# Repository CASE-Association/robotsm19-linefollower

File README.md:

# CASE line follower robot 2019
Project repository for CASE hardware and software developement for attending the Swedish Robotic Championship 2019.
The robot got 2nd place in the Swedish Robotic Championship 2019.

### Contributors
    -   Oskar Johansson
    -   Isak Åslund 
    -   Stefan Larsson

### Structure
    -   Software - All code for running the robot, implemented on Arduino   
    -   Hardware - PCB and hardware design
        -   Schematics for Arduino & STM32F103C8

### Pictures
[Picture album](https://imgur.com/a/kjrejrC)

**V0.1**

**V0.2**

**V1.0**

**PCB**
Two PCBs was designed, one for arduino and one for STM32.
Due to battery being applied to the VB pin on the STM32 it burned up. 
This caused us to use an arduino nano with breadboard instead. 
Since then a updated PCB has been made.

### Pinout Help
https://components101.com/microcontrollers/arduino-nano

### Info for development
IDE - Visual Studio Code + PlattformIO
If you want to simplify development change the formatter for cpp to the following:
"{ BasedOnStyle: Google, IndentWidth: 4, ColumnLimit: 0}", more info [here](https://stackoverflow.com/questions/46111834/format-curly-braces-on-same-line-in-c-vscode)

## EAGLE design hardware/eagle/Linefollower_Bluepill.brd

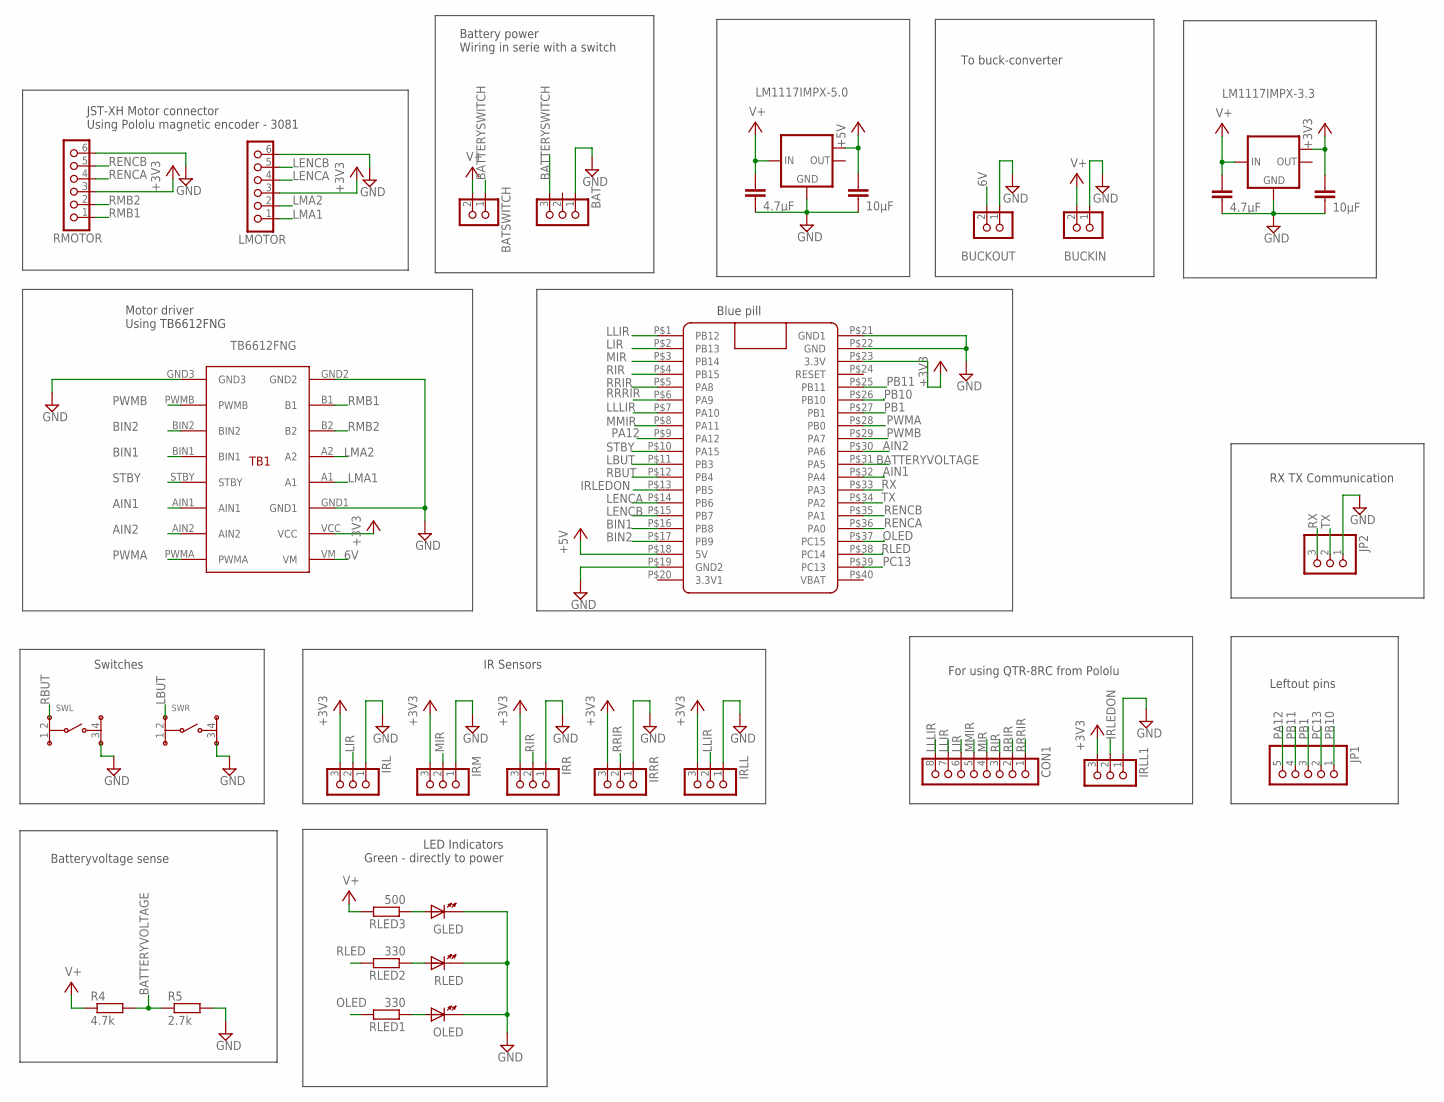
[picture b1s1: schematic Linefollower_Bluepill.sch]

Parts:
BAT: EH_B3B-EH; B3B-EH
BATSWITCH: EH_B2B-EH; B2B-EH
BUCKIN: EH_B2B-EH; B2B-EH
BUCKOUT: EH_B2B-EH; B2B-EH
C1, C3: 10µF; C0805
C2, C4: 4.7µF; C0805
CON1: EH_B8B-EH; B8B-EH
GLED: LED5MM
IC1: LM1117IMPX-5.0; SOT223
IC3: LM1117IMPX-3.3; SOT223
IRL: EH_B3B-EH; B3B-EH
IRLL, IRLL1: EH_B3B-EH; B3B-EH
IRM: EH_B3B-EH; B3B-EH
IRR: EH_B3B-EH; B3B-EH
IRRR: EH_B3B-EH; B3B-EH
JP1: PINHD-1X5; 1X05
JP2: PINHD-1X3; 1X03
LMOTOR: EH_B6B-EH; B6B-EH
OLED: LED5MM
R4: 4.7k; R0603
R5: 2.7k; R0603
RLED: LED5MM
RLED1, RLED2: 330; R0603
RLED3: 500; R0603
RMOTOR: EH_B6B-EH; B6B-EH
SWL: SKHHA/D
SWR: SKHHA/D
TB1: TB6612FNG
U$1: BLUE_PILL

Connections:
6V: BUCKOUT.2, TB1.VM
+3V3: C3.1, IC3.TAB (OUT1), IRL.3, IRLL.3, IRLL1.3, IRM.3, IRR.3, IRRR.3, LMOTOR.3, RMOTOR.3, TB1.VCC, U$1.P$23 (3.3V)
+5V: C1.1, IC1.TAB (OUT1), U$1.P$18 (5V)
AIN1: TB1.AIN1, U$1.P$32 (PA4)
AIN2: TB1.AIN2, U$1.P$30 (PA6)
BATTERYSWITCH: BAT.3, BATSWITCH.1
BATTERYVOLTAGE: R4.2, R5.1, U$1.P$31 (PA5)
BIN1: TB1.BIN1, U$1.P$16 (PB8)
BIN2: TB1.BIN2, U$1.P$17 (PB9)
GND: BAT.1, BUCKIN.1, BUCKOUT.1, C1.2, C2.2, C3.2, C4.2, GLED.K, IC1.1 (GND), IC3.1 (GND), IRL.1, IRLL.1, IRLL1.1, IRM.1, IRR.1, IRRR.1, JP2.1, LMOTOR.6, OLED.K, R5.2, RLED.K, RMOTOR.6, SWL.3, SWR.3, TB1.GND1, TB1.GND2, TB1.GND3, U$1.P$19 (GND2), U$1.P$21 (GND1), U$1.P$22 (GND)
IRLEDON: IRLL1.2, U$1.P$13 (PB5)
LBUT: SWR.2, U$1.P$11 (PB3)
LENCA: LMOTOR.4, U$1.P$14 (PB6)
LENCB: LMOTOR.5, U$1.P$15 (PB7)
LIR: CON1.6, IRL.2, U$1.P$2 (PB13)
LLIR: CON1.7, IRLL.2, U$1.P$1 (PB12)
LLLIR: CON1.8, U$1.P$7 (PA10)
LMA1: LMOTOR.1, TB1.A1
LMA2: LMOTOR.2, TB1.A2
MIR: CON1.4, IRM.2, U$1.P$3 (PB14)
MMIR: CON1.5, U$1.P$8 (PA11)
unnamed: GLED.A, RLED3.1
unnamed: RLED.A, RLED2.1
unnamed: OLED.A, RLED1.1
OLED: RLED1.2, U$1.P$37 (PC15)
PA12: JP1.5, U$1.P$9 (PA12)
PB1: JP1.3, U$1.P$27 (PB1)
PB10: JP1.1, U$1.P$26 (PB10)
PB11: JP1.4, U$1.P$25 (PB11)
PC13: JP1.2, U$1.P$39 (PC13)
PWMA: TB1.PWMA, U$1.P$28 (PB0)
PWMB: TB1.PWMB, U$1.P$29 (PA7)
RBUT: SWL.2, U$1.P$12 (PB4)
RENCA: RMOTOR.4, U$1.P$36 (PA0)
RENCB: RMOTOR.5, U$1.P$35 (PA1)
RIR: CON1.3, IRR.2, U$1.P$4 (PB15)
RLED: RLED2.2, U$1.P$38 (PC14)
RMB1: RMOTOR.1, TB1.B1
RMB2: RMOTOR.2, TB1.B2
RRIR: CON1.2, IRRR.2, U$1.P$5 (PA8)
RRRIR: CON1.1, U$1.P$6 (PA9)
RX: JP2.3, U$1.P$33 (PA3)
STBY: TB1.STBY, U$1.P$10 (PA15)
TX: JP2.2, U$1.P$34 (PA2)
V+: BATSWITCH.2, BUCKIN.2, C2.1, C4.1, IC1.3 (IN), IC3.3 (IN), R4.1, RLED3.2

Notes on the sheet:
JST-XH Motor connector Using Pololu magnetic encoder - 3081
Motor driver Using TB6612FNG
Battery power Wiring in serie with a switch
LED Indicators Green - directly to power
IR Sensors
Switches
Batteryvoltage sense
Blue pill
For using QTR-8RC from Pololu
Leftout pins
RX TX Communication
To buck-converter

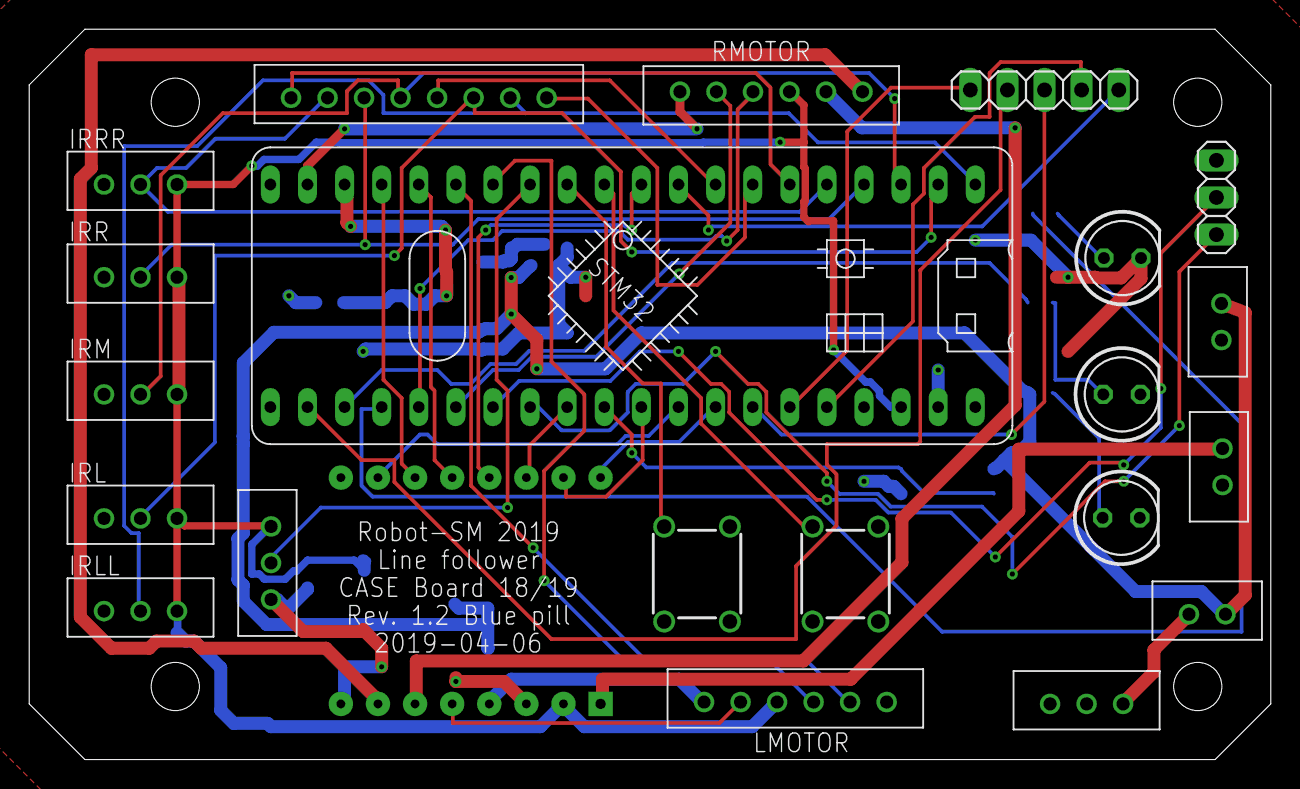
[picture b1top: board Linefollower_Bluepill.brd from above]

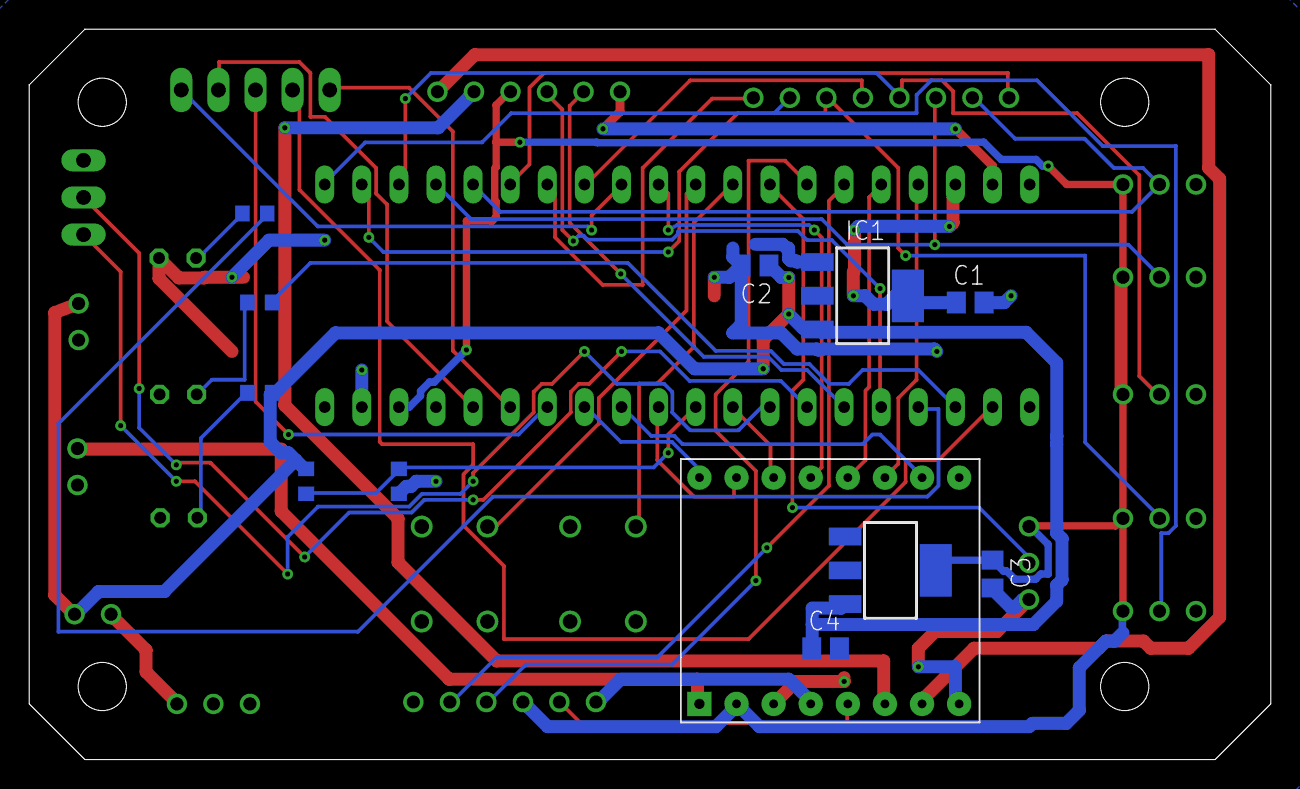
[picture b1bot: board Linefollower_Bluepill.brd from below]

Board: 2 copper layers, 85.0 x 50.0 mm, 33 parts (12 on the bottom side), 45 nets.

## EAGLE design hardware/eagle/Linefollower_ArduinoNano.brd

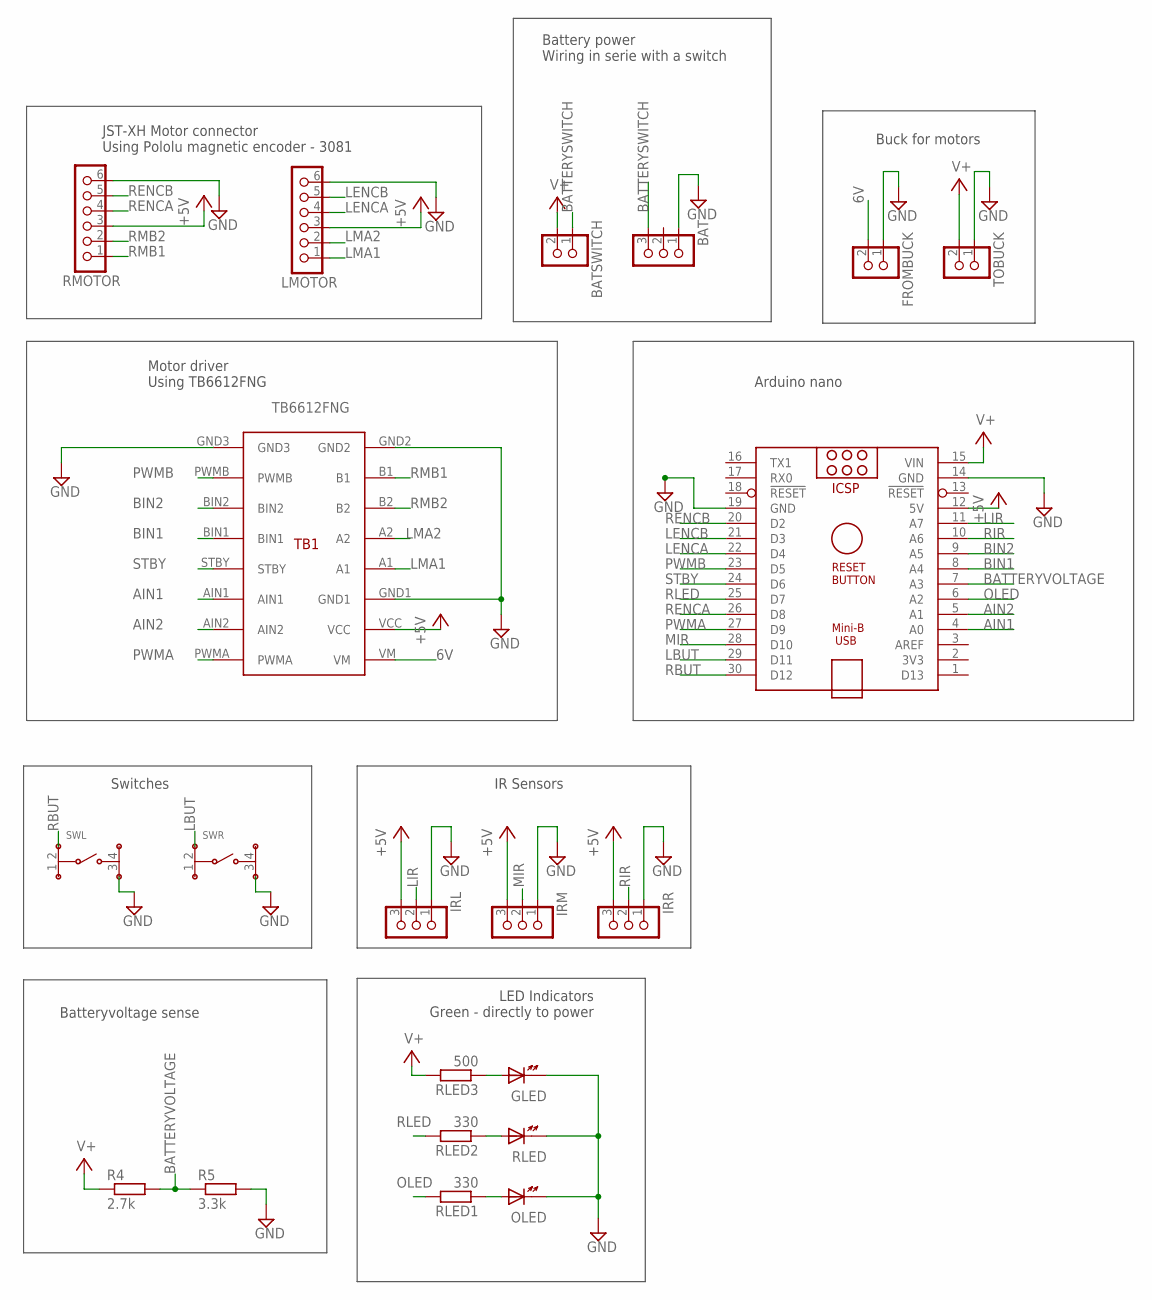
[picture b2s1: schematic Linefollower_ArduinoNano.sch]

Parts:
ARDUINO_NANO1: ARDUINO_NANO
BAT: EH_B3B-EH; B3B-EH
BATSWITCH: EH_B2B-EH; B2B-EH
FROMBUCK: EH_B2B-EH; B2B-EH
GLED: LED5MM
IRL: EH_B3B-EH; B3B-EH
IRM: EH_B3B-EH; B3B-EH
IRR: EH_B3B-EH; B3B-EH
LMOTOR: EH_B6B-EH; B6B-EH
OLED: LED5MM
R4: 2.7k; R0603
R5: 3.3k; R0603
RLED: LED5MM
RLED1, RLED2: 330; R0603
RLED3: 500; R0603
RMOTOR: EH_B6B-EH; B6B-EH
SWL: SKHHA/D
SWR: SKHHA/D
TB1: TB6612FNG
TOBUCK: EH_B2B-EH; B2B-EH

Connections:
6V: FROMBUCK.2, TB1.VM
+5V: ARDUINO_NANO1.12 (5V), IRL.3, IRM.3, IRR.3, LMOTOR.3, RMOTOR.3, TB1.VCC
AIN1: ARDUINO_NANO1.4 (A0), TB1.AIN1
AIN2: ARDUINO_NANO1.5 (A1), TB1.AIN2
BATTERYSWITCH: BAT.3, BATSWITCH.1
BATTERYVOLTAGE: ARDUINO_NANO1.7 (A3), R4.2, R5.1
BIN1: ARDUINO_NANO1.8 (A4), TB1.BIN1
BIN2: ARDUINO_NANO1.9 (A5), TB1.BIN2
GND: ARDUINO_NANO1.14 (GND), ARDUINO_NANO1.19 (GND), BAT.1, FROMBUCK.1, GLED.K, IRL.1, IRM.1, IRR.1, LMOTOR.6, OLED.K, R5.2, RLED.K, RMOTOR.6, SWL.3, SWR.3, TB1.GND1, TB1.GND2, TB1.GND3, TOBUCK.1
LBUT: ARDUINO_NANO1.29 (D11), SWR.2
LENCA: ARDUINO_NANO1.22 (D4), LMOTOR.4
LENCB: ARDUINO_NANO1.21 (D3), LMOTOR.5
LIR: ARDUINO_NANO1.11 (A7), IRL.2
LMA1: LMOTOR.1, TB1.A1
LMA2: LMOTOR.2, TB1.A2
MIR: ARDUINO_NANO1.28 (D10), IRM.2
unnamed: GLED.A, RLED3.1
unnamed: RLED.A, RLED2.1
unnamed: OLED.A, RLED1.1
OLED: ARDUINO_NANO1.6 (A2), RLED1.2
PWMA: ARDUINO_NANO1.27 (D9), TB1.PWMA
PWMB: ARDUINO_NANO1.23 (D5), TB1.PWMB
RBUT: ARDUINO_NANO1.30 (D12), SWL.2
RENCA: ARDUINO_NANO1.26 (D8), RMOTOR.4
RENCB: ARDUINO_NANO1.20 (D2), RMOTOR.5
RIR: ARDUINO_NANO1.10 (A6), IRR.2
RLED: ARDUINO_NANO1.25 (D7), RLED2.2
RMB1: RMOTOR.1, TB1.B1
RMB2: RMOTOR.2, TB1.B2
STBY: ARDUINO_NANO1.24 (D6), TB1.STBY
V+: ARDUINO_NANO1.15 (VIN), BATSWITCH.2, R4.1, RLED3.2, TOBUCK.2

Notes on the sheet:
JST-XH Motor connector Using Pololu magnetic encoder - 3081
Motor driver Using TB6612FNG
Battery power Wiring in serie with a switch
LED Indicators Green - directly to power
IR Sensors
Switches
Arduino nano
Batteryvoltage sense
Buck for motors

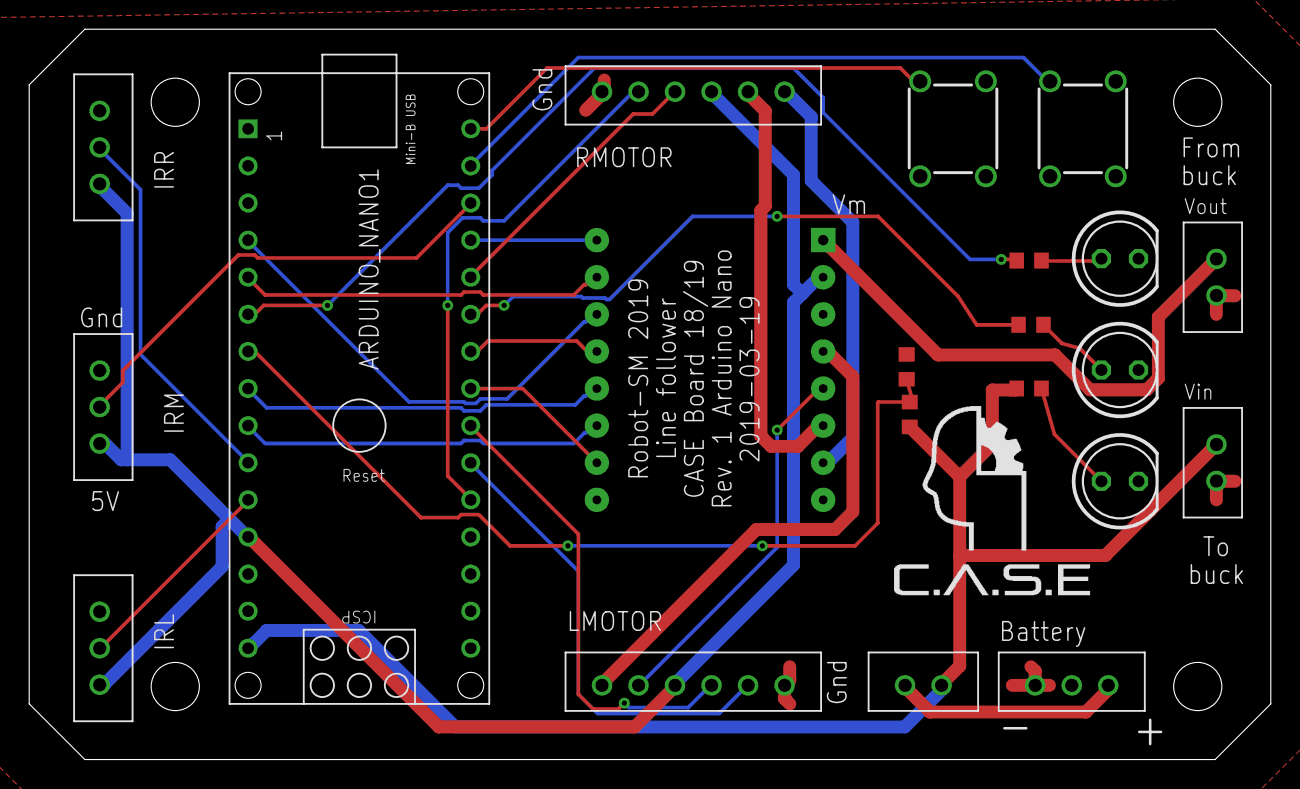
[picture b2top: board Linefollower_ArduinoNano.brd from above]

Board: 2 copper layers, 85.0 x 50.0 mm, 21 parts (1 on the bottom side), 31 nets.

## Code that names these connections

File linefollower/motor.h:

#ifndef MOTOR_H
#define MOTOR_H

#define AIN1 23 // A0
#define AIN2 24 // A1
#define BIN1 25 // A2
#define BIN2 26 // A3
#define STBY 27 // A4
#define PWMA 9  // Right Motor D9
#define PWMB 3  // Left Motor D3



void motorSetup(void);
void setLeftPWM(int);
void setRightPWM(int);



#endif

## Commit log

2019-03-10 Initial setup + Button/LED/Motor
    Initialization of the project and some of the LED/BUTTON/MOTOR functions.
2019-03-10 Motor functions
    Implementation for basic motor functionality
2019-03-10 Encoder implementation
2019-03-10 Encoder implementation (updated)
    Coded in the wrong repository so there was no implementation on the last commit. This one contains the implementation of the encoder.
2019-03-18 Updated plattform to PlattformIO
    Because the Arduino IDE gets cluttered with tabs and other stuff when the project gets larger we decided to switch the development plattform to "Plattform IO", we will now develop in visual studio co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
2019-03-18 Rewire + Cleanup
    Cleaned up code with formatting in VS CODE, soldered breadboard and had to redo some definitions becuase some pins were not compatible.
2019-03-18 LED Implementation + Verification
    LED now works as it should on hardware.
2019-03-18 Sensor implementation
    Implemeted IR line sensors (Flying-Fish MH-Sensor).
    Also did some motor testing and adjustments.
2019-03-19 encoder: cleanup
2019-03-19 First implementation of velocity control
    Not working because of different time standards.
2019-03-19 voltage: init commit
2019-03-19 Implemented tranlational control loop
2019-03-19 Updated README with Stefan
2019-03-19 Ok P values for trans/rot regulator
2019-03-19 Small Cleanup
2019-03-19 encoder: changed to register reads
2019-03-20 Redid implementation to be dumb
    No PID controller is no longer used fo turn and velocity. It is now dumb.
2019-03-24 Testing for STM32
2019-03-24 New folder structure
    Since a PCB was made the folder structure was changed to have both hardware and software.
2019-03-24 Rev 1.1
    This one was ordered 2019-03-20
2019-03-24 Rev 1
    This one was ordered 2019-03-20
2019-03-25 Added schematic PDF
2019-03-27 Change on silkmask
    Buck In and Buck Out was at wrong position.
2019-03-27 Hardware STL files
2019-03-27 First rev
    Only a basic base body. Not complete
2019-04-04 Rewrite of LED
2019-04-04 Rewrote Button
2019-04-04 Rewrote Motor
2019-04-04 Removed unecessary stuff from main
2019-04-04 Removed encoder
    It was removed since this project is done on arduino nano and there are not enough interrupt pins to make QTR sensor, and encoders
2019-04-04 Verified leds, sensors and motors
2019-04-04 no idea.....
2019-04-06 Robot SM 19 Final heat
    All code for final heat Robot SM 19. <10 s.
2019-04-06 QTR Sensor lib
    Library for QTR Sensor
2019-04-06 Removed Vin to VBat
    Removed wrong connection to bluepill. It caused the blue pill's magic smoke to escape. Resolves #4
2019-04-06 Updated layout.
2019-04-06 Updated with general information about the project
2019-04-06 2nd place not 3rd
2019-04-11 Updated with competition pic
